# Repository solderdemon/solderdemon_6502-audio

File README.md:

# SolderDemon 6502 Audio Board

## Overview

A YM2149F programmable sound generator card for the SolderDemon 6502 single-board computer, a descendant of [rosco_6502](https://github.com/rosco-m68k/rosco_6502) that keeps its expansion bus.

It is the 6502 sibling of the SolderDemon m68k Audio card and works the same way: the PSG sits behind a data latch and a GAL sequencer that times the strobes in hardware. The CPU stores a register number at `$C100` and a value at `$C101`; the card holds the CPU with `RDY` (the 6502's counterpart of `/DTACK`) for the ~4 µs the PSG needs. Three tone channels, noise and envelope, passive ABC stereo line out.

> **Status.** r1 fabrication files are available. Physical verification of this layout is pending. See the [build guide](docs/BUILD.md).

## Start here

- [KiCad project](design/solderdemon_6502-audio.kicad_pro)
- [Schematic (PDF)](manufacturing/solderdemon_6502-audio-schematic.pdf)
- [Build guide](docs/BUILD.md)
- [Gerbers and drill files](manufacturing/solderdemon_6502-audio-r1-2026-11-12-gerbers.zip)

## Board views

[3D render](images/solderdemon_6502-audio-3d.png)

| Top | Bottom |
|:---:|:---:|
|  |  |

## Hardware

### Highlights

- **Sound generator:** Yamaha **YM2149F** (`U1`, DIP-40), clocked by a **1.8432 MHz 5 V can** (`X1`) with `SEL` high.
- **Hardware-timed interface:** **ATF22V10C-7PX** (`U3`) decodes a write to `$C100–$C1FF`, pulls `RDY`, latches the byte into a **74HCT273** (`U2`), raises `BDIR` for two PSG clocks and drives `RDY` high again. `A0` drives `BC2` directly, `BC1` is grounded.
- **Shared-line hygiene:** `RDY` is enabled only in PHI2 high of the card's own write and driven high before it is let go (the host's pull-up is 3k3); it never sees an address-decode glitch.
- **Write-only, read-safe:** reads of the page do nothing and are not stretched; the PSG never drives the bus.
- **Passive ABC stereo:** A left, C right, B in both at about −6.9 dB; AC coupled, 100 kΩ bleeders.
- **Two outputs:** 3.5 mm **PJ-307** jack (`J2`, HOOYA, LCSC `C2939173`) on the top side edge, flush with the busboard's top (pin 1) edge, so it can go through a case wall like a PC card's bracket, and a 1×3 header (`J3`: L / GND / R).
- **Busboard form factor:** 72 × 100 mm, 2 layers, R4 corners, no mounting holes. 100 mm is the busboard's depth, so both side edges are flush with it and with the host; the card stands 69 mm tall. Copyright on the solder side.
- **100 % through-hole**, all ICs socketed.

### Memory Map

| Address | Access | Function |
|:---|:---|:---|
| **`$C100`** | write | PSG register number (A0 = 0 → `BC2` = 0: latch address) |
| **`$C101`** | write | value for that register (A0 = 1 → `BC2` = 1: write) |
| `$C102–$C1FF` | — | mirrors (A1–A7 not decoded); treat the page as occupied |
| reads | — | ignored, no wait state; the bus floats |

The DUART is at `$C000–$C00F`, the RAM board at `$CE00`/`$CF00` and `$D000–$DFFF`. `$C100` is this project's choice, not an upstream allocation.

### Operating Principle

```text
       SolderDemon 6502 bus (J1)
   A8..A15 PHI2 RWB ~RESET      D0..D7          A0
        |                        |              |
        v                        v              |
 +----------------+  CAPTURE +-----------+      |
 | U3 ATF22V10C-7 |--------->| U2 74HCT273|     |
 |  decode + 3-bit|          +-----------+      |
 |  Gray counter  |                | DA0..DA7   | BC2      BC1 = GND
 +----------------+  BDIR          v            v
   |  RDY  ^ CLK  -------->  +------------------------+
   v       |                 |       U1 YM2149F       |
  bus     X1 1.8432 MHz ---->|  CLOCK, SEL high       |
                             +------------------------+
                                A      B      C
                             1k loads, ABC mixer, 10 uF, 100k
                                  J2 3.5 mm / J3 L G R
```

1. **Request.** A write to `$C1xx` while `/RESET` is high. In PHI2 high `U3` pulls `RDY` low; the W65C02S holds and repeats the write cycle.
2. **Capture.** `CAPTURE` rises at every PHI2 fall of the held cycle, so `U2` holds the byte.
3. **Count.** The 3-bit Gray counter, clocked by `X1`, starts on the first edge that sees PHI2 high and stops capturing at state 3.
4. **Strobe.** `BDIR` is high in states 4–5: 1085 ns, with `BC2` = `A0` and the data stable for at least 543 ns before and after.
5. **Release.** At state 7 `RDY` is driven high; the CPU finishes the cycle, the address changes, `U3` lets go of `RDY` and resets.

Timing budget: [docs/TIMING.md](docs/TIMING.md).

### Compared with rosco_6502-audio

The card replaces the first SolderDemon attempt, `rosco_6502-audio` moved onto the SolderDemon socket unchanged (never built): a W65C22S VIA drove `BC1`/`BDIR` from software, with `NOP`s timing the strobe, an ATF16V8 decoded the VIA and a 2.000 MHz can clocked the PSG.

| | rosco_6502-audio port | r1 |
|---|---|---|
| Bus interface | W65C22S VIA + ATF16V8B decoder | ATF22V10C-7 sequencer + 74HCT273 latch, as on the m68k card |
| PSG write | 2 VIA stores per strobe, 4 per register, timed by `NOP` | 2 plain stores: register number, value |
| Strobe length | 0.5–6 µs, set by the CPU clock; NMI or single-step could break 10 µs | 1.09 µs from the PSG clock, at any CPU clock |
| CPU clock | 1–10 MHz | any, to 14 MHz |
| PSG clock | 2.000 MHz, on Yamaha's limit | 1.8432 MHz, as on the m68k card |
| Bus lines | A0–A3, A8–A15, `~IRQ` (diode) | A0, A8–A15, `RDY`; no `~IRQ` |
| ICs | 3 + can (2 × DIP-40) | 3 + can |
| Board | 100 × 90 mm, R4 | 72 × 100 mm: as deep as the busboard, 72 mm high; jack on the side |

What r1 gives up: the VIA's timers and interrupt. Playback ticks come from the host (the DUART timer).

## Using the board

### Programming Example

```asm
PSG_REG  = $C100
PSG_DATA = $C101

; A = value, X = register. IRQs off so a handler cannot get between the two stores.
psg_write:
    php
    sei
    pha
    txa
    and #$0F
    sta PSG_REG         ; register number
    pla
    sta PSG_DATA        ; value
    plp
    rts
```

`code/software/demo/psg.s` has `psg_write`, `psg_init` (all registers 0, mixer `$3F`), `psg_silence` and `psg_test_chord` (C4–E4–G4 at 1.8432 MHz: periods 440, 349, 294). There is no delay anywhere: the card holds the CPU as long as it needs.

```sh
ca65 code/software/demo/psg.s -l code/software/demo/psg.lst
ca65 code/software/demo/demo.s
ld65 -C code/software/demo/demo.cfg -o code/software/demo/demo.bin -m code/software/demo/demo.map -Ln code/software/demo/demo.lbl code/software/demo/demo.o code/software/demo/psg.o
```

The demo loads at `$1000`: `JSR $1000` leaves the chord playing.

## Build and verification

### Bill of Materials

| Reference | Value | Package | Notes |
|:---|:---|:---|:---|
| **U1** | YM2149F | DIP-40, 15.24 mm | Socket it. AliExpress lots are not guaranteed genuine. |
| **U2** | 74HCT273 | DIP-20 | Data latch. HCT, not HC: its D inputs see the CPU bus. |
| **U3** | ATF22V10C-7PX | DIP-24, 7.62 mm | Sequencer. **-7** needed for `RDY` at 14 MHz; -10/-15 only to 10 MHz. Power-down off. |
| **X1** | 1.8432 MHz, 5 V | Oscillator DIP-8 | Can, not a crystal. Pin 1 enable or NC. |
| **J1** | 2×18 female, right angle | 2.54 mm | The host's `J5` footprint, component side. |
| **J2** | PJ-307 | 3.5 mm TRS, horizontal | S = GND, T = left, R = right, switch pins unused. |
| **J3** | 1×3 header | 2.54 mm | L / GND / R. |
| **R1, R2** | 33 Ω | Axial | Clock series resistors to U1 and U3. |
| **R3, R4** | 10 kΩ | Axial | `BDIR` and `CAPTURE` pull-downs. |
| **R5–R7** | 1 kΩ | Axial | Channel loads A/B/C (1 % preferred). |
| **R8, R11** | 10 kΩ | Axial | A → left, C → right. |
| **R9, R10** | 22 kΩ | Axial | B → left and right. |
| **R12, R13** | 100 kΩ | Axial | Output bleeders. |
| **C1–C4** | 100 nF | Radial, 5.08 mm pitch | U1, U2, U3, X1. |
| **C5** | 47 µF / 16 V | Radial D6.3 mm | Bulk at J1. |
| **C6, C7** | 10 µF / 16 V | Radial D6.3 mm | Output coupling, `+` to the mixer. |

Plus sockets: 1 × DIP-40, 1 × DIP-24, 1 × DIP-20. [BOM.csv](design/BOM.csv). Budget 250 mA at 5 V (not measured). Keep parts under about 11 mm for the 20 mm slot pitch.

### PLD Firmware (U3)

Source `code/firmware/pld/audio_sequencer.pld` (GALasm), image `code/firmware/pld/audio_sequencer.jed`:

```sh
galasm code/firmware/pld/audio_sequencer.pld
minipro -p ATF22V10C -w code/firmware/pld/audio_sequencer.jed
```

Program as ATF22V10C, verify after writing. Do not use an ATF16V8: neither the pins nor the fuse map fit.

### First Power-Up

1. Power off: check `J1` orientation, electrolytic polarity, no +5 V–GND short; check X1's pin 1 function.
2. Program and verify `U3`. Fit the ICs by their pin 1 marks.
3. Run the host at 1–2 MHz first. 5 V on `U1`-40, `U2`-20, `U3`-24; 1.8432 MHz on `U1`-22; `U3`-21 (BDIR) low.
4. Line out to active speakers or an amplifier (≥ 10 kΩ), not headphones.
5. Load `code/software/demo/demo.bin` at `$1000`, `JSR $1000`: a C–E–G chord.
6. On a scope, per store: `J1`-12 (RDY) low ~4 µs, `U3`-21 (BDIR) one 1.09 µs pulse, `U3`-22 (CAPTURE) rising at PHI2 falls before it. Check CAPTURE against D0–D7 at the highest clock you intend to run (docs/TIMING.md, capture hold).

### Files

- **KiCad 10 project:** [design/](design/)
- **Libraries:** `SolderDemonAudio.kicad_sym` (bus, sequencer), `SolderDemonAudio.pretty/`: the host's `PinSocket_2x18_P2.54mm_Horizontal_EdgeMount`, the PJ-307 jack (stock, and `_EdgeMount` with the silk cut at the board edge, which `build_card.py` writes), the SolderDemon logo
- **Schematic PDF:** [Schematic](manufacturing/solderdemon_6502-audio-schematic.pdf); **BOM:** [BOM.csv](design/BOM.csv)
- **Gerbers:** [manufacturing/solderdemon_6502-audio-r1-2026-11-12-gerbers.zip](manufacturing/solderdemon_6502-audio-r1-2026-11-12-gerbers.zip), unpacked in [manufacturing/gerbers/](manufacturing/gerbers/)
- **PCB:** 2 layers, 100 × 72 mm in the files (69 mm tall in the slot, 100 mm deep), 1.6 mm FR-4, 1 oz, GND pour on both layers, no mounting holes
- **J1 geometry:** the busboard specification gives pin 1 at `(5.775, 14.425)` mm from the top-left corner with the bus edge on the left, as the host's `J5`. The KiCad files show the card a quarter turn round, bus edge down as on the m68k card: there pin 1 sits at `(14.425, 63.225)` and the board is 100 × 72 mm. The bus edge goes into the slot, the opposite edge stands up, and the jack (on the left in the files) leaves through the side at the busboard's pin 1 edge. `PIN 1` and a triangle mark the socket, which hides the square pad.

#### Verification

| Check | Result |
|---|---|
| ERC | [solderdemon_6502-audio-erc.rpt](solderdemon_6502-audio-erc.rpt): 0 |
| DRC + schematic parity | [solderdemon_6502-audio-drc.rpt](solderdemon_6502-audio-drc.rpt): 0 / 0 unconnected / 0 parity |
| `tools/verify_design.py` | [verification.txt](verification.txt): pads vs schematic vs design.json; `J1` against the host's `J5` pad by pad and signal by signal; U3's fuse map over all addresses × R/W × reset × PHI2; YM2149 strapping |
| `tools/sim_card.py` | [sim-verification.txt](sim-verification.txt): 30 timed runs, 870 PSG writes through the fuse map with address glitches, repeated held cycles, DUART/neighbour cycles, RMW; register file, one `BDIR` per write, Yamaha set-up/hold/width, latch contents, `RDY` timing and scope |
| `tools/verify_driver.py` | [driver-verification.txt](driver-verification.txt): the ca65 binary on py65 against the register model |

The sim proves the logic and the model's timing, not the silicon.

#### Rebuilding

The board is generated, not edited by hand: change `tools/build_card.py` (circuit and placement) or the `.pld`, then run the chain. A KiCad edit is lost on the next run.

```sh
K="C:/Program Files/KiCad/10.0/bin"
(cd code/firmware/pld && galasm audio_sequencer.pld)
"$K/python.exe" tools/build_card.py      # schematic, symbols, unrouted board, design.json, BOM, bus-reference.xml
python tools/sim_card.py                 # timed simulation from design.json + .jed
"$K/python.exe" tools/route_card.py      # ../tools/route_lib.py: Freerouting swarm, GND pour, cleanup
"$K/kicad-cli.exe" sch erc -o solderdemon_6502-audio-erc.rpt design/solderdemon_6502-audio.kicad_sch
"$K/kicad-cli.exe" pcb drc --schematic-parity --severity-error --severity-warning -o solderdemon_6502-audio-drc.rpt design/solderdemon_6502-audio.kicad_pcb
"$K/python.exe" tools/verify_design.py
python tools/verify_driver.py
"$K/python.exe" tools/make_outputs.py             # Gerbers, drill, zip, schematic PDF, renders
```

### Sources

[Yamaha YM2149 datasheet](https://www.ym2149.com/ym2149.pdf), [WDC W65C02S datasheet](https://www.westerndesigncenter.com/wdc/documentation/w65c02s.pdf), [Microchip ATF22V10C datasheet](https://ww1.microchip.com/downloads/en/DeviceDoc/doc0735.pdf). The bus pinout comes from the local `solderdemon_6502` host schematic (`bus-reference.xml`, rewritten by every build).

### Reproducing the board

The KiCad project and the fabrication package can be used directly from this repository. Place the SolderDemon 6502 mainboard checkout beside this checkout for bus verification and schematic generation. Full autorouting and packaging use the shared SolderDemon hardware workspace tools.

For the optional jack model, use the [PJ-307 vendor model](https://lcsc.com/product-detail/audio-connectors_hooya-pj-307_C2939173.html) and save it as `design/3d/PJ-307.step`.

<!-- repository-layout -->
## Repository layout

- [`design/`](design/solderdemon_6502-audio.kicad_pro) holds the KiCad project, schematic, PCB and local libraries.
- [`code/firmware/`](code/firmware/) — Sequencer equations and JEDEC programming files.
- [`code/software/`](code/software/) — The PSG driver and ca65 demo.
- [`code/build/`](code/build/) — Local build products.
- [`tools/`](tools/) — Design generators and verification.
- [`manufacturing/`](manufacturing/) — Fabrication files and schematic PDF.
- [`images/`](images/) — Board views and artwork.

Open the project in `design/`. Use the scripts in `tools/` to change the design. The `.kicad_pro` file holds the DRC rules.
<!-- /repository-layout -->

## Licences and attribution

- **Hardware:** [CERN Open Hardware Licence v1.2](LICENCE.hardware.txt).
- **Code:** [MIT](LICENSE.code), covering the driver, demo, PLD source and tools.

Copyright © 2026 solderdemon_6502-audio contributors. The card follows the [rosco_6502](https://github.com/rosco-m68k/rosco_6502) expansion interface for compatibility. Original rosco_6502 authorship: Ross Bamford & Contributors. Retained third-party notices identify their respective sources.

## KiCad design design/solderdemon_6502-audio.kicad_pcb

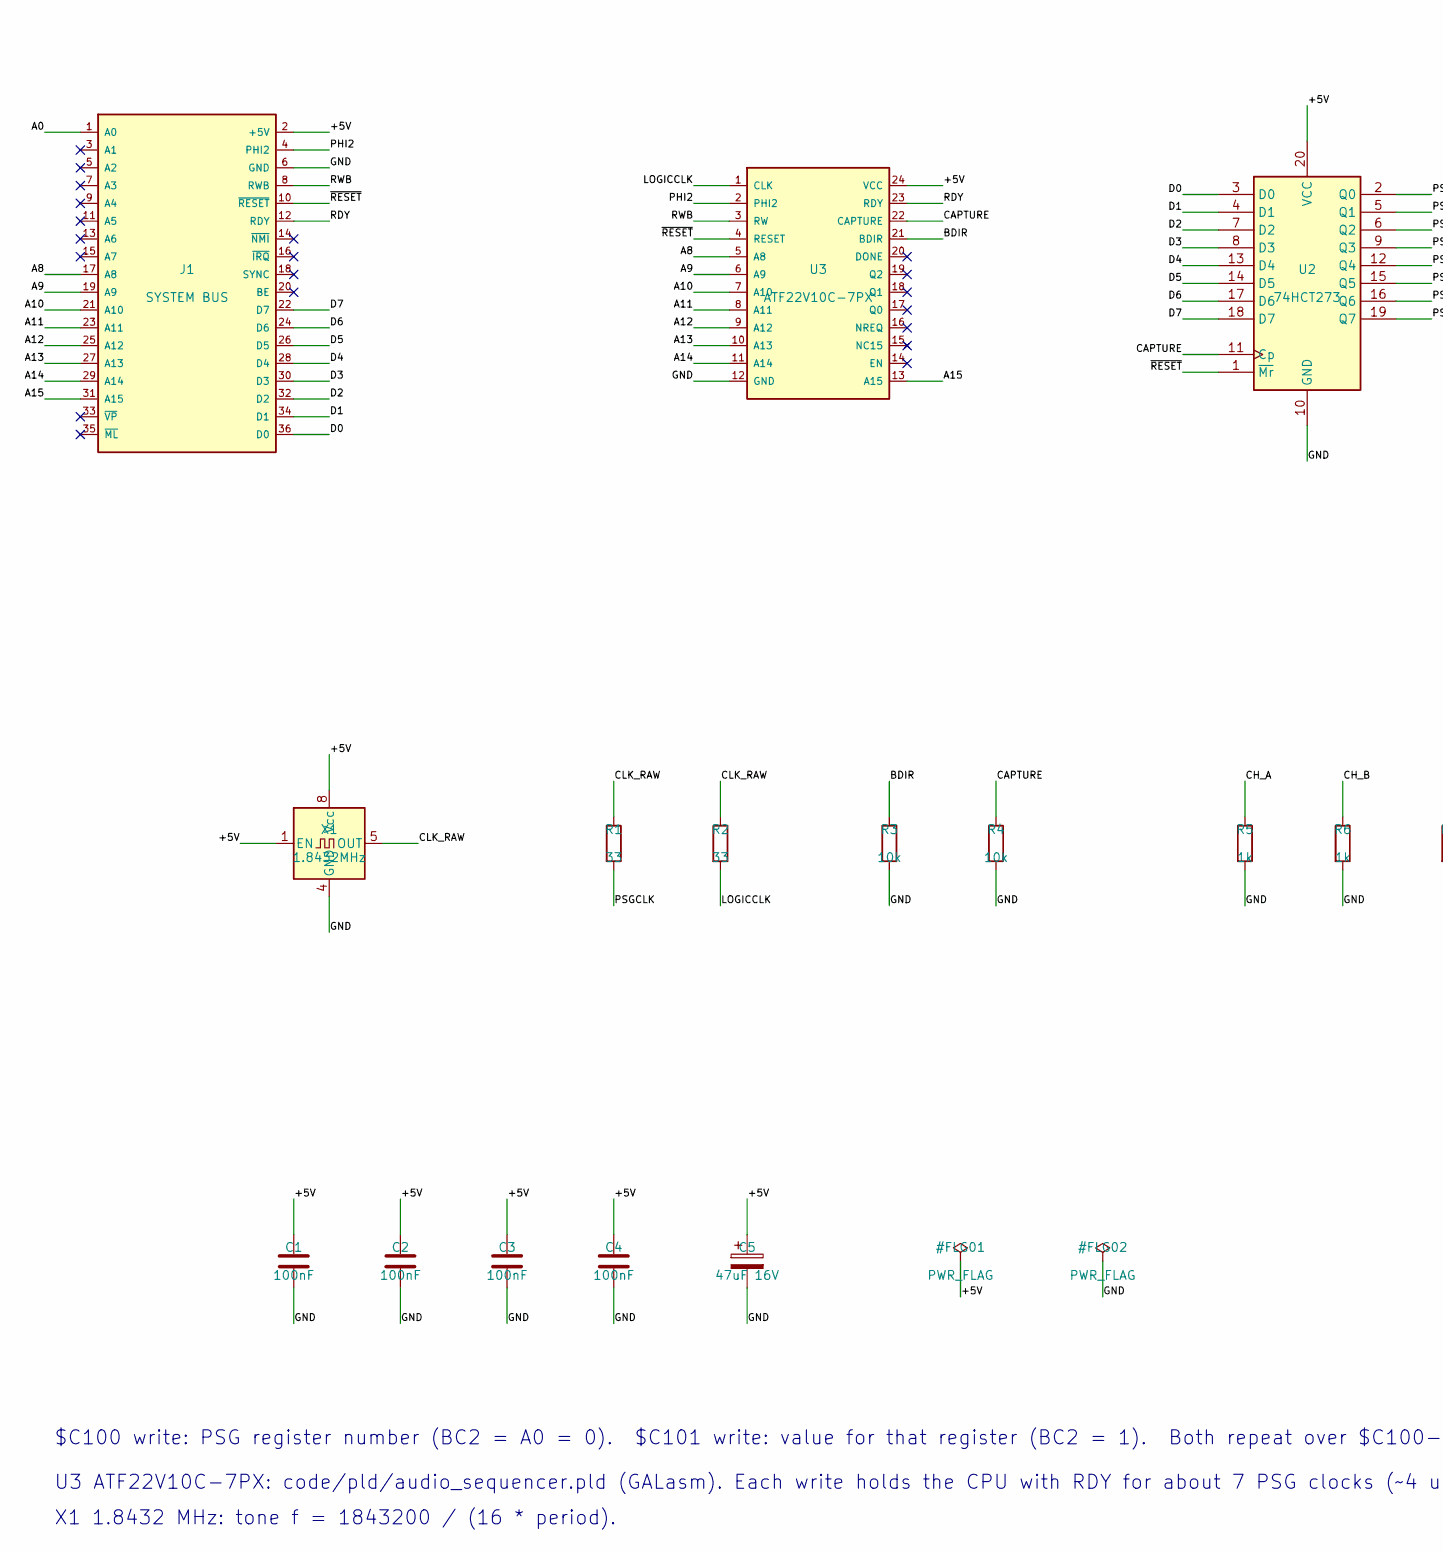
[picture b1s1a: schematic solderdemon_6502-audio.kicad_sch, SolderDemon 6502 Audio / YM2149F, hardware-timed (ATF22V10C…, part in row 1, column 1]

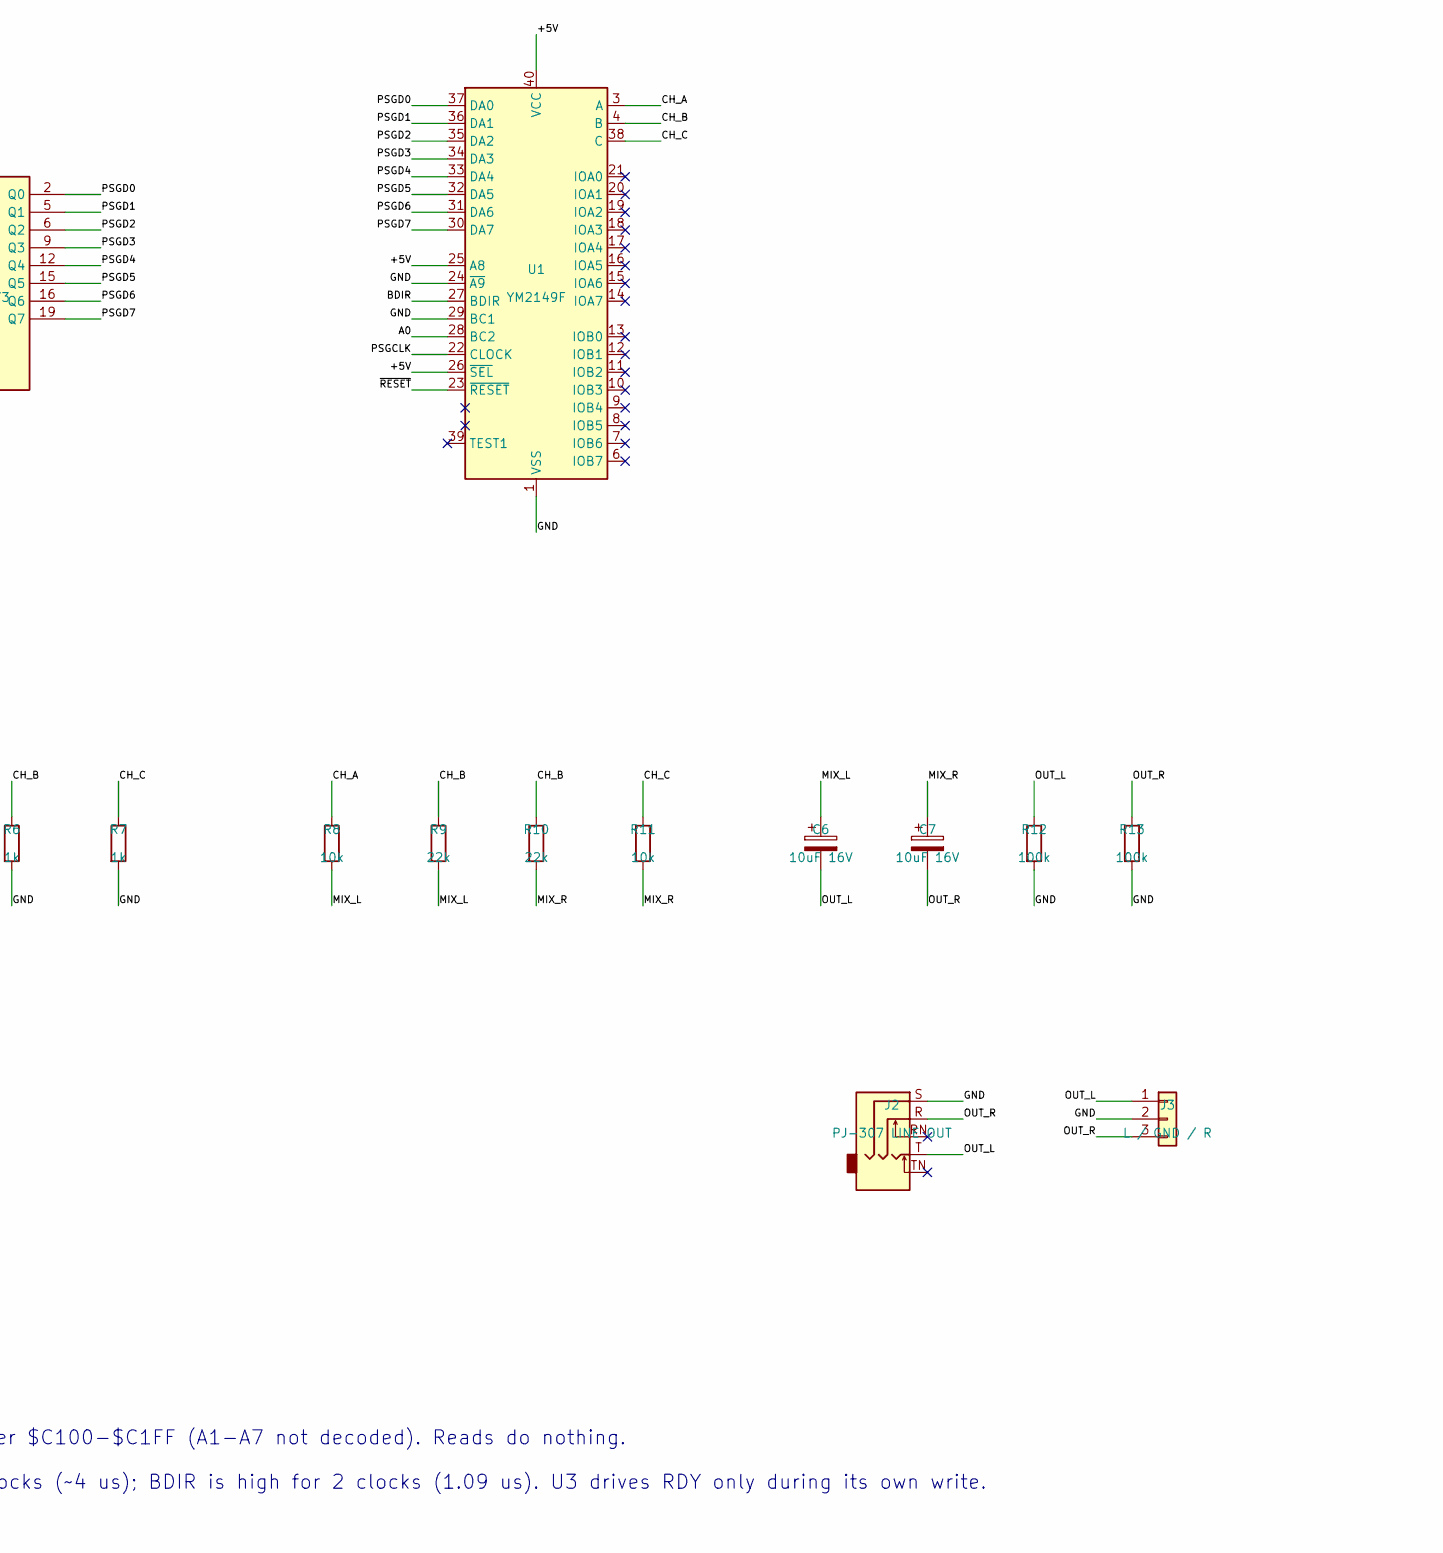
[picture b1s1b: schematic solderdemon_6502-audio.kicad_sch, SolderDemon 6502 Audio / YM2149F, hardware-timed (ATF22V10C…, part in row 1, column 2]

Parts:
C1, C2, C3, C4: 100nF; C_Radial_5.08mm
C5: 47uF 16V; CP_Radial_D6.3mm_P2.50mm
C6, C7: 10uF 16V; CP_Radial_D6.3mm_P2.50mm
J1: SYSTEM BUS; PinSocket_2x18_P2.54mm_Horizontal_EdgeMount
J2: PJ-307 LINE OUT; Jack_3.5mm_HOOYA_PJ-307_Horizontal_EdgeMount
J3: L / GND / R; PinHeader_1x03_P2.54mm_Vertical
R1, R2: 33; R_Axial_DIN0207_L6.3mm_D2.5mm_P7.62mm_Horizontal
R3, R4, R8, R11: 10k; R_Axial_DIN0207_L6.3mm_D2.5mm_P7.62mm_Horizontal
R5, R6, R7: 1k; R_Axial_DIN0207_L6.3mm_D2.5mm_P7.62mm_Horizontal
R9, R10: 22k; R_Axial_DIN0207_L6.3mm_D2.5mm_P7.62mm_Horizontal
R12, R13: 100k; R_Axial_DIN0207_L6.3mm_D2.5mm_P7.62mm_Horizontal
U1: YM2149F; DIP-40_W15.24mm_Socket_LongPads
U2: 74HCT273; DIP-20_W7.62mm_Socket_LongPads
U3: ATF22V10C-7PX; DIP-24_W7.62mm_Socket_LongPads
X1: 1.8432MHz; Oscillator_DIP-8

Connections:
/+5V: C1.1, C2.1, C3.1, C4.1, C5.1, J1.2 (+5V), U1.25 (A8), U1.26 (~SEL), U1.40 (VCC), U2.20 (VCC), U3.24 (VCC), X1.1 (EN), X1.8 (Vcc)
/A0: J1.1 (A0), U1.28 (BC2)
/A8: J1.17 (A8), U3.5 (A8)
/A9: J1.19 (A9), U3.6 (A9)
/A10: J1.21 (A10), U3.7 (A10)
/A11: J1.23 (A11), U3.8 (A11)
/A12: J1.25 (A12), U3.9 (A12)
/A13: J1.27 (A13), U3.10 (A13)
/A14: J1.29 (A14), U3.11 (A14)
/A15: J1.31 (A15), U3.13 (A15)
/BDIR: R3.1, U1.27 (BDIR), U3.21 (BDIR)
/CAPTURE: R4.1, U2.11 (Cp), U3.22 (CAPTURE)
/CH_A: R5.1, R8.1, U1.3 (A)
/CH_B: R6.1, R9.1, R10.1, U1.4 (B)
/CH_C: R7.1, R11.1, U1.38 (C)
/CLK_RAW: R1.1, R2.1, X1.5 (OUT)
/D0: J1.36 (D0), U2.3 (D0)
/D1: J1.34 (D1), U2.4 (D1)
/D2: J1.32 (D2), U2.7 (D2)
/D3: J1.30 (D3), U2.8 (D3)
/D4: J1.28 (D4), U2.13 (D4)
/D5: J1.26 (D5), U2.14 (D5)
/D6: J1.24 (D6), U2.17 (D6)
/D7: J1.22 (D7), U2.18 (D7)
/GND: C1.2, C2.2, C3.2, C4.2, C5.2, J1.6 (GND), J2.S, J3.2, R3.2, R4.2, R5.2, R6.2, R7.2, R12.2, R13.2, U1.1 (VSS), U1.24 (~A9), U1.29 (BC1), U2.10 (GND), U3.12 (GND), X1.4 (GND)
/LOGICCLK: R2.2, U3.1 (CLK)
/MIX_L: C6.1, R8.2, R9.2
/MIX_R: C7.1, R10.2, R11.2
/OUT_L: C6.2, J2.T, J3.1, R12.1
/OUT_R: C7.2, J2.R, J3.3, R13.1
/PHI2: J1.4 (PHI2), U3.2 (PHI2)
/PSGCLK: R1.2, U1.22 (CLOCK)
/PSGD0: U1.37 (DA0), U2.2 (Q0)
/PSGD1: U1.36 (DA1), U2.5 (Q1)
/PSGD2: U1.35 (DA2), U2.6 (Q2)
/PSGD3: U1.34 (DA3), U2.9 (Q3)
/PSGD4: U1.33 (DA4), U2.12 (Q4)
/PSGD5: U1.32 (DA5), U2.15 (Q5)
/PSGD6: U1.31 (DA6), U2.16 (Q6)
/PSGD7: U1.30 (DA7), U2.19 (Q7)
/RDY: J1.12 (RDY), U3.23 (RDY)
/RWB: J1.8 (RWB), U3.3 (RW)
/~RESET: J1.10 (~RESET), U1.23 (~RESET), U2.1 (~Mr), U3.4 (RESET)

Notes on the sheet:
$C100 write: PSG register number (BC2 = A0 = 0). $C101 write: value for that register (BC2 = 1). Both repeat over $C100-$C1FF (A1-A7 not decoded). Reads do nothing.
U3 ATF22V10C-7PX: code/pld/audio_sequencer.pld (GALasm). Each write holds the CPU with RDY for about 7 PSG clocks (~4 us); BDIR is high for 2 clocks (1.09 us). U3 drives RDY only during its own write.
X1 1.8432 MHz: tone f = 1843200 / (16 * period).

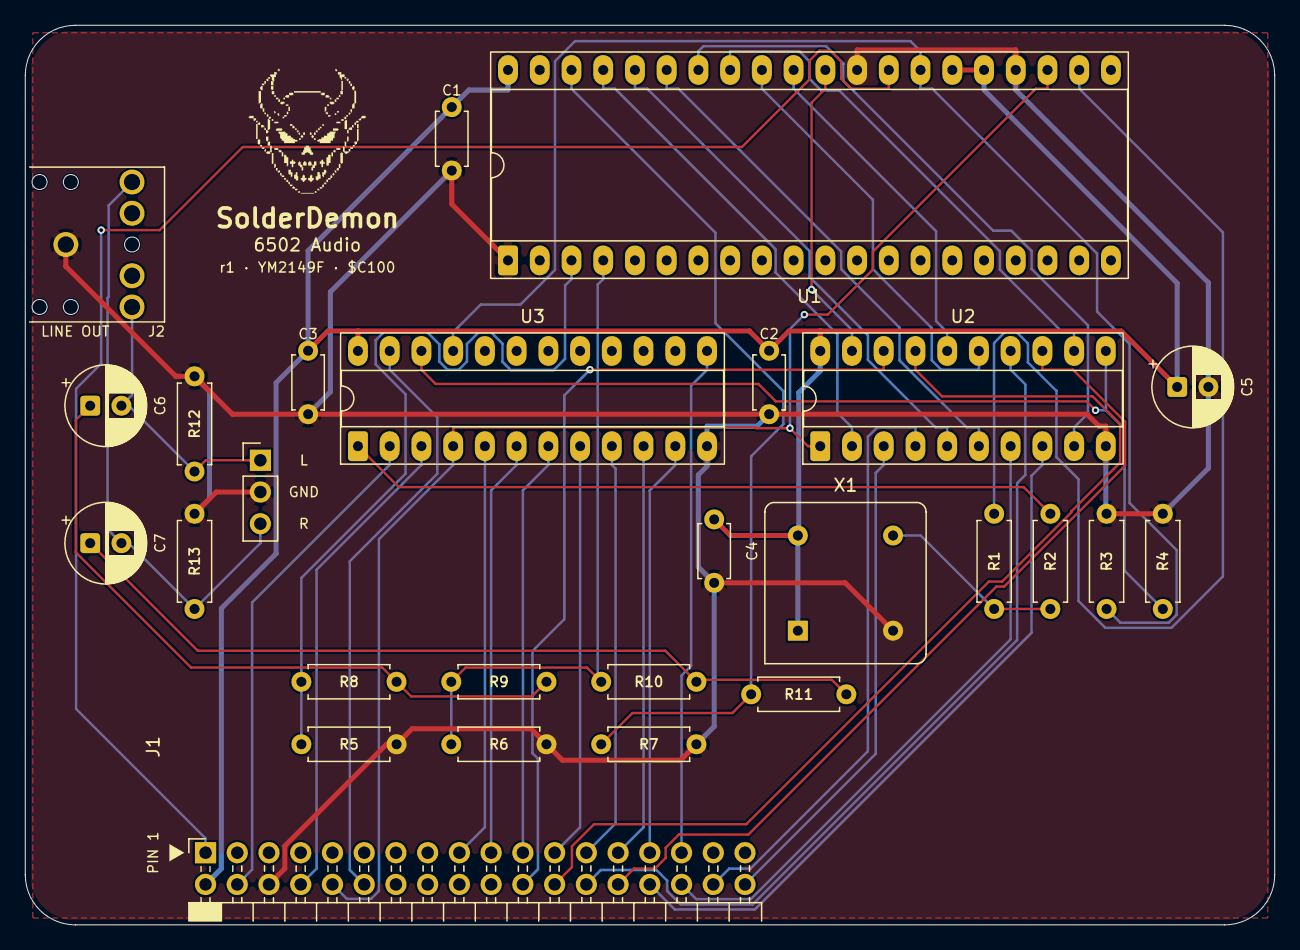
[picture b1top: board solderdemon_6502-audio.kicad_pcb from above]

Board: 2 copper layers, 100.0 x 72.0 mm, 28 parts (0 on the bottom side), 43 nets.

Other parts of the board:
LOGO1: SolderDemon_Logo

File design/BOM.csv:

Reference,Value,Footprint
J1,SYSTEM BUS,SolderDemonAudio:PinSocket_2x18_P2.54mm_Horizontal_EdgeMount
U3,ATF22V10C-7PX,Package_DIP:DIP-24_W7.62mm_Socket_LongPads
U2,74HCT273,Package_DIP:DIP-20_W7.62mm_Socket_LongPads
U1,YM2149F,Package_DIP:DIP-40_W15.24mm_Socket_LongPads
X1,1.8432MHz,Oscillator:Oscillator_DIP-8
R1,33,Resistor_THT:R_Axial_DIN0207_L6.3mm_D2.5mm_P7.62mm_Horizontal
R2,33,Resistor_THT:R_Axial_DIN0207_L6.3mm_D2.5mm_P7.62mm_Horizontal
R3,10k,Resistor_THT:R_Axial_DIN0207_L6.3mm_D2.5mm_P7.62mm_Horizontal
R4,10k,Resistor_THT:R_Axial_DIN0207_L6.3mm_D2.5mm_P7.62mm_Horizontal
R5,1k,Resistor_THT:R_Axial_DIN0207_L6.3mm_D2.5mm_P7.62mm_Horizontal
R6,1k,Resistor_THT:R_Axial_DIN0207_L6.3mm_D2.5mm_P7.62mm_Horizontal
R7,1k,Resistor_THT:R_Axial_DIN0207_L6.3mm_D2.5mm_P7.62mm_Horizontal
R8,10k,Resistor_THT:R_Axial_DIN0207_L6.3mm_D2.5mm_P7.62mm_Horizontal
R9,22k,Resistor_THT:R_Axial_DIN0207_L6.3mm_D2.5mm_P7.62mm_Horizontal
R10,22k,Resistor_THT:R_Axial_DIN0207_L6.3mm_D2.5mm_P7.62mm_Horizontal
R11,10k,Resistor_THT:R_Axial_DIN0207_L6.3mm_D2.5mm_P7.62mm_Horizontal
C6,10uF 16V,Capacitor_THT:CP_Radial_D6.3mm_P2.50mm
C7,10uF 16V,Capacitor_THT:CP_Radial_D6.3mm_P2.50mm
R12,100k,Resistor_THT:R_Axial_DIN0207_L6.3mm_D2.5mm_P7.62mm_Horizontal
R13,100k,Resistor_THT:R_Axial_DIN0207_L6.3mm_D2.5mm_P7.62mm_Horizontal
J2,PJ-307 LINE OUT,SolderDemonAudio:Jack_3.5mm_HOOYA_PJ-307_Horizontal_EdgeMount
J3,L / GND / R,Connector_PinHeader_2.54mm:PinHeader_1x03_P2.54mm_Vertical
C1,100nF,SolderDemonCaps:C_Radial_5.08mm
C2,100nF,SolderDemonCaps:C_Radial_5.08mm
C3,100nF,SolderDemonCaps:C_Radial_5.08mm
C4,100nF,SolderDemonCaps:C_Radial_5.08mm
C5,47uF 16V,Capacitor_THT:CP_Radial_D6.3mm_P2.50mm

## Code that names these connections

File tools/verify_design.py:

"""Check the board against its own schematic, against the SolderDemon 6502 host and against the PLD.

    "C:/Program Files/KiCad/10.0/bin/python.exe" tools/verify_design.py

  - every pad carries the net design.json and the KiCad netlist (schematic.xml) give it;
  - J1 is the host's J5: same footprint and side, every pad at the same offset from the outline's
    corner (BACKPLANE.md of the busboard), the card drawn a quarter turn round, bus edge down, and on every pin the signal the
    host drives (bus-reference.xml, the host schematic's netlist);
  - U3's fuse map, for all 65536 addresses: a write selects exactly $C100-$C1FF (RDY enabled in
    PHI2 high, CAPTURE low), a read or reset selects nothing, and RDY is never driven while PHI2
    is low unless the sequencer has started;
  - the YM2149 strapping: BC1 grounded, BC2 = A0, chip address /A9 = 0, A8 = 1, SEL high, and
    nothing but U3 and the bus on RDY.
"""
from pathlib import Path
import json, sys, xml.etree.ElementTree as ET
import pcbnew as p

root = Path(__file__).resolve().parents[1]
sys.path.insert(0, str(Path(__file__).parent))
import gal

HOST = root.parent / 'solderdemon_6502' / 'design' / 'solderdemon_6502.kicad_pcb'
SAME = {'VCC': '+5V', 'CLK': 'PHI2', 'R/~{W}': 'RWB', 'IRQ': '~{IRQ}', 'NMI': '~{NMI}'}   # host net -> card net
parts = json.loads((root / 'design/design.json').read_text())
b = p.LoadBoard(str(root / 'design/solderdemon_6502-audio.kicad_pcb'))


def netlist(path, ref=None):
    out = {}
    for net in ET.parse(path).findall('./nets/net'):
        for node in net.findall('node'):
            if ref is None or node.attrib['ref'] == ref:
                out[(node.attrib['ref'], node.attrib['pin'])] = net.attrib['name']
    return out


sch = netlist(root / 'design/schematic.xml')
errors = []
for part in parts:
    if part['ref'].startswith('#'): continue
    fp = b.FindFootprintByReference(part['ref'])
    for pin, net in part['nets'].items():
        pads = [a for a in fp.Pads() if a.GetNumber() == pin]
        assert pads, (part['ref'], pin)
        for a in pads:
            actual = a.GetNetname().removeprefix('/')
            if net and actual != net: errors.append(('PCB', part['ref'], pin, net, actual))
            if not net and actual and not actual.startswith('unconnected-'): errors.append(('NC', part['ref'], pin, actual))
        actual = sch.get((part['ref'], pin), '').removeprefix('/')
        if net and actual != net: errors.append(('SCH', part['ref'], pin, net, actual))


def corner(board):
    outline = p.SHAPE_POLY_SET()
    assert board.GetBoardPolygonOutlines(outline, False)
    box = outline.BBox()
    return box.GetX(), box.GetY()


# J1 against the host's J5, pad by pad, from each outline's top-left corner. The card's files show
# it a quarter turn anticlockwise from the host's (bus edge down), so a host offset (x, y) is the
# card's (y, h - x), h being the card's height in this view.
host = p.LoadBoard(str(HOST))
f, hf = b.FindFootprintByReference('J1'), host.FindFootprintByReference('J5')
assert f.GetFPID().GetLibItemName() == hf.GetFPID().GetLibItemName(), (f.GetFPIDAsString(), hf.GetFPIDAsString())
assert f.IsFlipped() == hf.IsFlipped() == False and (f.GetOrientationDegrees() - hf.GetOrientationDegrees()) % 360 == 90
outline = p.SHAPE_POLY_SET(); assert b.GetBoardPolygonOutlines(outline, False)
h = outline.BBox().GetHeight()
(cx, cy), (hx, hy) = corner(b), corner(host)
hpads = {a.GetNumber(): a for a in hf.Pads()}
for a in f.Pads():
    hp = hpads[a.GetNumber()]
    ox, oy = hp.GetPosition().x - hx, hp.GetPosition().y - hy
    assert (a.GetPosition().x - cx, a.GetPosition().y - cy) == (oy, h - ox), a.GetNumber()
pin1 = next(a for a in f.Pads() if a.GetNumber() == '1').GetPosition()
assert (p.ToMM(pin1.x - cx), p.ToMM(cy + h - pin1.y)) == (14.425, 5.775)
bus = netlist(root / 'design/bus-reference.xml', 'J5')
for a in f.Pads():
    want = SAME.get(bus[('J5', a.GetNumber())], bus[('J5', a.GetNumber())])
    got = a.GetNetname().removeprefix('/')
    if got.startswith('unconnected-'):
        got = got.split('-')[2] if got.count('-') >= 3 else got   # unconnected-(J1-<pin name>-PadN)
    if got != want: errors.append(('BUS', a.GetNumber(), want, a.GetNetname()))

# U3 from its fuses: every address, write and read, in and out of reset, PHI2 high and low.
src = (root / 'code/firmware/pld/audio_sequencer.pld').read_text()
name = gal.pins(src); pin = {n: k for k, n in name.items()}
g = gal.Gal22V10(gal.jedec((root / 'code/firmware/pld/audio_sequencer.jed').read_text()))
selected = []
for addr in range(0, 0x10000, 0x100):                     # A0-A7 do not reach U3
    for rw in (0, 1):
        for reset in (1, 0):
            for phi2 in (1, 0):
                lv = {pin[f'A{i}']: addr >> i & 1 for i in range(8, 16)}
                lv.update({pin['RW']: rw, pin['RESET']: reset, pin['PHI2']: phi2})
                g.q = {k: 0 for k in g.q}                    # sequencer idle (AR holds it so between writes)
                lv[pin['NREQ']] = 1
                for _ in range(3):                           # NREQ and EN feed back through their pins
                    out = g.outputs(lv)
                    lv.update({pin['NREQ']: out[pin['NREQ']], pin['EN']: out[pin['EN']]})
                req = out[pin['NREQ']] == 0
                rdy_on = out[pin['RDY']] is not None
                if req != (out[pin['CAPTURE']] == 0) and phi2: errors.append(('CAPTURE', hex(addr), rw, reset))
                if rdy_on != (req and phi2): errors.append(('RDY enable', hex(addr), rw, reset, phi2))
                if rdy_on and out[pin['RDY']] != 0: errors.append(('RDY idle level', hex(addr)))
                if out[pin['BDIR']]: errors.append(('BDIR idle', hex(addr)))
                if req and phi2: selected.append((addr, rw, reset))
assert [a for a, rw, reset in selected] == [0xC100] and selected[0][1:] == (0, 1), selected

# YM2149 strapping and the shared RDY line.
ym = next(x for x in parts if x['ref'] == 'U1')['nets']
assert (ym['29'], ym['28'], ym['24'], ym['25'], ym['26']) == ('GND', 'A0', 'GND', '+5V', '+5V'), ym
rdy = sorted(k for k, n in sch.items() if n.removeprefix('/') == 'RDY')
assert rdy == [('J1', '12'), ('U3', '23')], rdy
assert not errors, errors
result = ('PASS: schematic/PCB/manifest connectivity; J1 = host J5 (36 pads, offsets and signals); '
          'U3 fuse map over 65536 addresses x R/W x reset x PHI2 (selects $C100-$C1FF writes only, RDY only in '
          'PHI2 high until the sequencer runs); YM2149 strapping; RDY only on U3 and J1.\n')
(root / 'verification.txt').write_text(result)
print(result)
